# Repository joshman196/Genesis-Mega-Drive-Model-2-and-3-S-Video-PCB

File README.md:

# Sega Genesis/Mega Drive Model 2 & 3 S-Video Mod PCB

Simple PCB that carries Luma, Chroma, and Ground lines with their respective components. Available as a standard through hole version or a nano/super nano surface-mount version. If unsure, just go with the Standard PCB. This should work on consoles that contain the following video encoders: Sony CXA1645, Fujitsu MB3514, and Sony CXA2075. This will **NOT** work with Model 2 consoles that contain a Samsung KA2195D video encoder, this is due to that encoder not carrying the necessary lines to drive S-Video. Only the CXA1645 in a VA4 Model 2 has been tested with these PCBs so far. If you have a model 1 Genesis/Mega Drive with a CXA1145 encoder, use the [Model 1 S-Video PCB](https://github.com/joshman196/Simple-Genesis-Model-1-S-Video-Private/tree/main).

**It is recommended to use 28 AWG wire for this install.**

## Parts Needed

**Only order the parts you need for the board type you are building for.**

### "Standard" PCB

- 2x 220µF 6.3v Capacitors
- 2x 75 Ohm Resistors

You can buy these components in a kit from [console5.com](https://console5.com/store/cxa1645-s-video-mod-kit.html). Make sure to also pick up an S-Video jack as well, and conveniently enough console5 also offers these in either [socket](https://console5.com/store/mini-din-in-line-socket-4-pin-female-black-pin-type-s-video-s-vhs.html) or [panel mount](https://console5.com/store/s-video-jacks-panel-mount-black-plastic-housing-solder-type.html) configurations. The version you get depends on whether you want to drill the outer shell of your console (flush mount) or not (socket).

### "Nano" and "Super Nano" PCBs

- 2x 220µF 6.3v 1411 (3528 Metric) Tantalum Capacitors (Tantalum Polymers recommended) - [Digikey Part](https://www.digikey.com/en/products/detail/kyocera-avx/TCJB227M006R0070/2615437)
- 2x 75 Ohm 0805 (2012 Metric) Resistors - [Digikey Part](https://www.digikey.com/en/products/detail/yageo/RC0805FR-0775RL/728132)

Make sure to also pick up an S-Video jack as well. You can get these from console5.com in either [socket](https://console5.com/store/mini-din-in-line-socket-4-pin-female-black-pin-type-s-video-s-vhs.html) or [panel mount](https://console5.com/store/s-video-jacks-panel-mount-black-plastic-housing-solder-type.html) configurations. The version you get depends on whether you want to drill the outer shell of your console (flush mount) or not (socket).

## Installation Steps

1. Add the capacitors/resistors to the PCB and find a suitable place inside your console to put the assembled board at. You may want to put kapton tape on the area of the main board where you plan on setting the PCB at. You may also choose to set it somewhere off of the main board.
2. Connect a wire from pin 15 of the CXA1645/MB3514 to "C In" on the S-Video PCB.
3. Connect a wire from pin 16 of the CXA1645/MB3514 to "Y In" on the S-Video PCB.
4. Connect a wire from pin 1 of the CXA1645/MB3514 to "GND" on the S-Video PCB.
5. If you have heatshrink tubing that you want to use, you should prepare them on the next set of wires below before soldering the other ends of those wires. **Do not apply the heat to the tubing until after testing your install!**
6. Connect a wire from "C Out" on the S-Video PCB to the Chroma pin on the back of the S-Video jack.
7. Connect a wire from "Y Out" on the S-Video PCB to the Luma/Y pin on the back of the S-Video jack.
8. Connect a wire from "CGND" on the S-Video PCB to the Chroma-Ground pin on the back of the S-Video jack.
9. Connect a wire from "YGND" on the S-Video PCB to the Luma/Y-Ground pin on the back of the S-Video jack.
10. With the wiring all done, stick some more kapton tape from the sides over the PCB to stick it down onto the main board itself, setting the PCB on top of the other layer of kapton tape you put earlier. DO NOT SET THE PCB DOWN ON THE BARE MAIN BOARD WITHOUT SOME KIND OF INSULATION UNDER THE S-VIDEO PCB TO PREVENT POTENTIAL SHORTS. Electrical tape may work but that tends to leave a nasty residue, so I wouldn't recommend it.
11. You're done!

## Board Types

### "Standard" Through-Hole PCB (~33.274mm x ~16.891mm)

### "Nano" Surface-Mount PCB (~16.002mm x ~8.179mm)

### "Super Nano" Surface-Mount PCB (~9.423mm x ~7.468mm)

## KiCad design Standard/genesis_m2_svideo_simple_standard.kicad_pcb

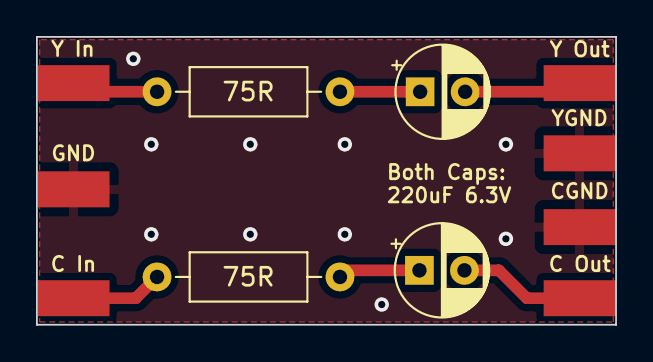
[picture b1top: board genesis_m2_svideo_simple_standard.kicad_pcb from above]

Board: 2 copper layers, 32.2 x 16.0 mm, 11 parts (0 on the bottom side), 7 nets.

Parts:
C1, C2: 220uF 6.3V; CP_Radial_D5.0mm_P2.50mm
J1: Y In; SolderWirePad_1x01_SMD_2x4mm
J2: C In; SolderWirePad_1x01_SMD_2x4mm
J3: Y Out; SolderWirePad_1x01_SMD_2x4mm
J4: C Out; SolderWirePad_1x01_SMD_2x4mm
J5: GND; SolderWirePad_1x01_SMD_2x4mm
J6: YGND; SolderWirePad_1x01_SMD_2x4mm
J7: CGND; SolderWirePad_1x01_SMD_2x4mm
R1, R2: 75R; R_Axial_DIN0207_L6.3mm_D2.5mm_P10.16mm_Horizontal

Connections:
GND: J5.1, J6.1, J7.1
unnamed: C1.1, R1.2
unnamed: C2.1, R2.2
unnamed: J1.1, R1.1
unnamed: J2.1, R2.1
unnamed: C1.2, J3.1
unnamed: C2.2, J4.1

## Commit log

2023-08-20 initial file upload
2024-01-23 super nano - minor update
2024-01-23 nano - minor update
2024-01-23 standard - minor update
